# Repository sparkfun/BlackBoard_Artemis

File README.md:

SparkFun BlackBoard Artemis
============================

[  
*SparkFun BlackBoard (SPX-15332)*](https://www.sparkfun.com/products/15332)

Think of the BlackBoard Artemis as just another Arduino... That has BLE. And one meg of flash. And runs at less than 1mA. Oh, and it can run TensorFlow models. Ya, that too. The BlackBoard Artemis takes the incredibly powerful Artemis module from SparkFun and wraps it up in an easy to use and familiar Uno footprint. We've written an Arduino core from scratch to make programming the Artemis as familiar as `Serial.begin(9600)`. Time-to-first-blink is less than five minutes.

The BlackBoard Artemis has the improved power conditioning and USB to serial that we've refined over the years on our BlackBoard line of products. A modern USB-C connector makes programming easy. A Qwiic connector makes I<sup>2</sup>C easy. The BlackBoard Artemis is fully compatible with SparkFun's Arduino core and can be programmed easily under the Arduino IDE. We've exposed the JTAG connector for more advanced users who prefer to use the power and speed of professional tools. We've added a digital MEMS microphone for folks wanting to experiment with always-on voice commands with TensorFlow and machine learning. We've even added a convenient jumper to measure current consumption for low power testing.

With 1M flash and 384k RAM you'll have plenty of room for your sketches. The Artemis module runs at 48MHz with a 96MHz turbo mode available and with Bluetooth to boot!

The SparkFun BlackBoard Artemis is a great platform to 'kick the tires' of this amazing module. If you're interesting in testing out the full capabilities of the SparkFun Artemis module or if you're looking for more compact solution, be sure to checkout our ATP and Nano versions of the Artemis line.

**Note:** We are actively working on getting FCC and compliance certifications for the SparkFun Artemis Module. Once our certifications are complete we will be moving the BlackBoard to a RedBoard format with the FCC Certified version of the Artemis on board. *Please be aware* that this could happen as soon as a few weeks to a month so this BlackBoard version is for those of you who can't wait and want to start using the SparkFun Artemis as soon as possible!

Repository Contents
-------------------
* **/Hardware** - Eagle design files (.brd, .sch)

Documentation
-------------------
* **[Hookup Guide for the BlackBoard Artemis](https://learn.sparkfun.com/tutorials/hookup-guide-for-the-blackboard-artemis)**
* **[Designing with the SparkFun Artemis](https://learn.sparkfun.com/tutorials/designing-with-the-sparkfun-artemis)** - Layout and design considerations when using the Artemis module.
* **[Artemis Development with Arduino](https://learn.sparkfun.com/tutorials/artemis-development-with-arduino)** - Introduction to the Arduino core for the Artemis Module.
* **[Ambiq Apollo3 SDK SetUp](https://learn.sparkfun.com/tutorials/using-sparkfun-edge-board-with-ambiq-apollo3-sdk)** - Getting set up with the Apollo3 Software Development Kit.
* **[CH340E USB to serial IC Drivers](https://www.sparkfun.com/ch340)**
* **[SparkFun Fritzing repo](https://github.com/sparkfun/Fritzing_Parts)** - Fritzing diagrams for SparkFun products.
License Information
-------------------

This product is _**open source**_! 

Please review the LICENSE.md file for license information. 

If you have any questions or concerns on licensing, please contact techsupport@sparkfun.com.

Please use, reuse, and modify these files as you see fit. Please maintain attribution to SparkFun Electronics and release any derivative under the same license.

Distributed as-is; no warranty is given.

- Your friends at SparkFun.

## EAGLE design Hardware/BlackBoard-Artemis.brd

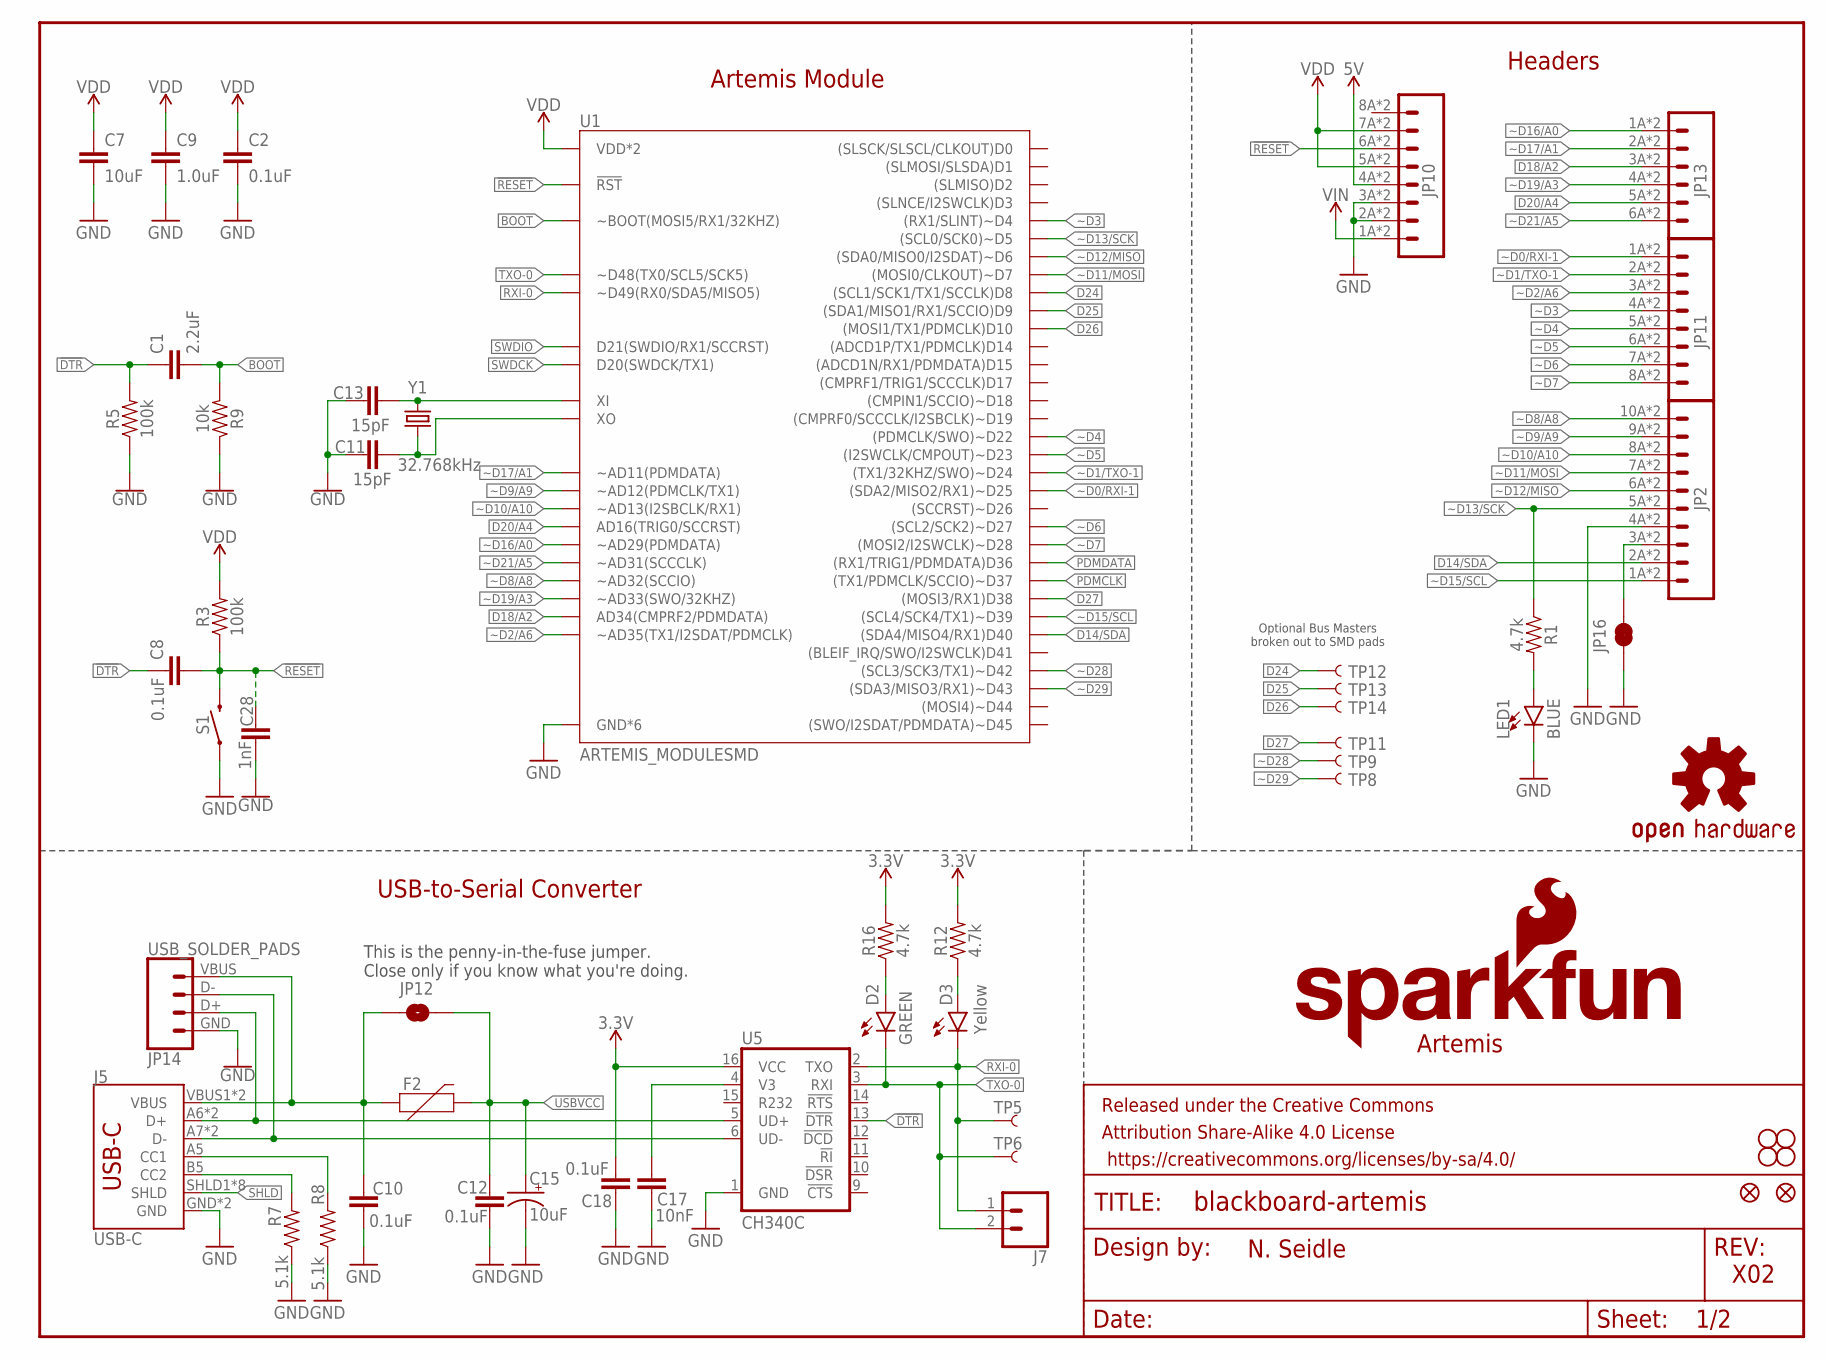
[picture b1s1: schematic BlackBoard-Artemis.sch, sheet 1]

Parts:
C1: 2.2uF; 0603
C2, C8, C10, C12, C18: 0.1uF; 0603
C7: 10uF; 0603
C9: 1.0uF; 0603
C11, C13: 15pF; 0603
C15: 10uF; EIA3216
C17: 10nF; 0603
C28: 1nF; 0603
D2: GREEN; LED-1206
D3: Yellow; LED-1206
F2: 6V/2A; 1210
FRAME1: FRAME-LETTER; CREATIVE_COMMONS
J5: USB-C; USB-C-16P
J7: CONN_021X02_NO_SILK; 1X02_NO_SILK
JP1: SFE_LOGO_NAME.1_INCH; SFE_LOGO_NAME_.1
JP2: M10SMD_COMBO; 1X10_SMD_COMBINED
JP3, JP4, JP5, JP6: STAND-OFF
JP7: SFE_LOGO_FLAME.1_INCH; SFE_LOGO_FLAME_.1
JP8, JP9: FIDUCIAL1X2; FIDUCIAL-1X2
JP10: M08SMD-COMBO; 1X08_SMD_COMBINED
JP11: JP11; 1X08_SMD_COMBINED
JP12: JUMPER-SMT_2_NO_SILK; SMT-JUMPER_2_NO_SILK
JP13: M06SMD-STRAIGHT-COMBO; 1X06_SMD_STRAIGHT_COMBO
JP14: USB_SOLDER_PADS; USB-SOLDER-PADS
JP16: JUMPER-SMT_2_NC_TRACE_SILK; SMT-JUMPER_2_NC_TRACE_SILK
LED1: BLUE; LED-1206
R1, R12, R16: 4.7k; 0603
R3, R5: 100k; 0603
R7, R8: 5.1k; 0603
R9: 10k; 0603
S1: MOMENTARY-SWITCH-SPST-SMD-5.2-TALL-REDUNDANT; TACTILE_SWITCH_SMD_5.2MM
TP5, TP6, TP8, TP9, TP11, TP12, TP13, TP14: TEST-POINT3X5; PAD.03X.05
U1: ARTEMIS_MODULESMD; ARTEMIS_FP
U5: CH340C; SO016
U$16: OSHW-LOGOS; OSHW-LOGO-S
Y1: 32.768kHz; CRYSTAL-SMD-3.2X1.5MM

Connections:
3.3V: C18.1, R12.2, R16.2, U5.16 (VCC); also elsewhere on the board
5V: JP10.4A (4), JP10.4B (4); also elsewhere on the board
!DTR: C1.1, C8.1, R5.2, U5.13 (!DTR)
!RESET: C8.2, C28.1, JP10.6A (6), JP10.6B (6), R3.1, S1.3 (2), S1.4 (2), U1.~RST (!RST); also elsewhere on the board
BOOT: C1.2, R9.2, U1.BOOT (~BOOT(MOSI5/RX1/32KHZ))
CC1: J5.A5 (CC1), R8.2
CC2: J5.B5 (CC2), R7.2
D14/SDA: JP2.2A (2), JP2.2B (2), U1.D40 ((SDA4/MISO4/RX1)D40); also elsewhere on the board
D18/A2: JP13.3A (3), JP13.3B (3), U1.AD34 (AD34(CMPRF2/PDMDATA))
D20/A4: JP13.5A (5), JP13.5B (5), U1.AD16 (AD16(TRIG0/SCCRST))
D24: TP12.P$1, U1.D8 ((SCL1/SCK1/TX1/SCCLK)D8)
D25: TP13.P$1, U1.D9 ((SDA1/MISO1/RX1/SCCIO)D9)
D26: TP14.P$1, U1.D10 ((MOSI1/TX1/PDMCLK)D10)
D27: TP11.P$1, U1.D38 ((MOSI3/RX1)D38)
D+: J5.A6 (D+), J5.B6 (D+), JP14.D+ (3), U5.5 (UD+)
D-: J5.A7 (D-), J5.B7 (D-), JP14.D- (2), U5.6 (UD-)
GND: C2.1, C7.2, C9.2, C10.2, C11.1, C12.2, C13.1, C15.-, C17.2, C18.2, C28.2, J5.GND, J5.GND2 (GND), JP2.4A (4), JP2.4B (4), JP10.2A (2), JP10.2B (2), JP10.3A (3), JP10.3B (3), JP14.GND (4), JP16.1, LED1.C, R5.1, R7.1, R8.1, R9.1, S1.1, S1.2 (1), U1.GND@1 (GND*6), U1.GND@22 (GND*6), U1.GND@38 (GND*6), U1.GND@39 (GND*6), U1.GND@47 (GND*6), U1.GND@59 (GND*6), U5.1 (GND); also elsewhere on the board
unnamed: LED1.A, R1.2
unnamed: D2.A, R16.1
unnamed: C17.1, U5.4 (V3)
unnamed: C11.2, U1.XO, Y1.P$2 (2)
unnamed: C13.2, U1.XI, Y1.P$1 (1)
unnamed: D3.A, R12.1
unnamed: JP2.3A (3), JP2.3B (3), JP16.2
PDMCLK: U1.~D37 ((TX1/PDMCLK/SCCIO)~D37); also elsewhere on the board
PDMDATA: U1.D36 ((RX1/TRIG1/PDMDATA)D36); also elsewhere on the board
RXI-0: D3.C, J7.1, TP5.P$1, U1.RXI-0 (~D49(RX0/SDA5/MISO5)), U5.2 (TXO)
SHLD: J5.SHLD1 (SHLD), J5.SHLD2 (SHLD), J5.SHLD3 (SHLD), J5.SHLD4 (SHLD), J5.SHLD5 (SHLD), J5.SHLD6 (SHLD), J5.SHLD7 (SHLD), J5.SHLD8 (SHLD)
SWDCK: U1.SWDCK (D20(SWDCK/TX1)); also elsewhere on the board
SWDIO: U1.SWDIO (D21(SWDIO/RX1/SCCRST)); also elsewhere on the board
TXO-0: D2.C, J7.2, TP6.P$1, U1.TXO-0 (~D48(TX0/SCL5/SCK5)), U5.3 (RXI)
USBVCC: C12.1, C15.+, F2.2, JP12.2; also elsewhere on the board
VDD: C2.2, C7.1, C9.1, JP10.5A (5), JP10.5B (5), JP10.7A (7), JP10.7B (7), R3.2, U1.VDD@36 (VDD*2), U1.VDD@37 (VDD*2); also elsewhere on the board
VIN: JP10.1A (1), JP10.1B (1); also elsewhere on the board
VUSB: C10.1, F2.1, J5.VBUS1 (VBUS), J5.VBUS2 (VBUS), JP12.1, JP14.VBUS (1)
~D0/RXI-1: JP11.1A (1), JP11.1B (1), U1.~D25 ((SDA2/MISO2/RX1)~D25)
~D1/TXO-1: JP11.2A (2), JP11.2B (2), U1.~D24 ((TX1/32KHZ/SWO)~D24)
~D2/A6: JP11.3A (3), JP11.3B (3), U1.~AD35 (~AD35(TX1/I2SDAT/PDMCLK))
~D3: JP11.4A (4), JP11.4B (4), U1.~D4 ((RX1/SLINT)~D4)
~D4: JP11.5A (5), JP11.5B (5), U1.~D22 ((PDMCLK/SWO)~D22)
~D5: JP11.6A (6), JP11.6B (6), U1.~D23 ((I2SWCLK/CMPOUT)~D23)
~D6: JP11.7A (7), JP11.7B (7), U1.~D27 ((SCL2/SCK2)~D27)
~D7: JP11.8A (8), JP11.8B (8), U1.~D28 ((MOSI2/I2SWCLK)~D28)
~D8/A8: JP2.10A (10), JP2.10B (10), U1.~AD32 (~AD32(SCCIO))
~D9/A9: JP2.9A (9), JP2.9B (9), U1.~AD12 (~AD12(PDMCLK/TX1))
~D10/A10: JP2.8A (8), JP2.8B (8), U1.~AD13 (~AD13(I2SBCLK/RX1))
~D11/MOSI: JP2.7A (7), JP2.7B (7), U1.D7 ((MOSI0/CLKOUT)~D7)
~D12/MISO: JP2.6A (6), JP2.6B (6), U1.~D6 ((SDA0/MISO0/I2SDAT)~D6)
~D13/SCK: JP2.5A (5), JP2.5B (5), R1.1, U1.~D5 ((SCL0/SCK0)~D5)
~D15/SCL: JP2.1A (1), JP2.1B (1), U1.~D39 ((SCL4/SCK4/TX1)~D39); also elsewhere on the board
~D16/A0: JP13.1A (1), JP13.1B (1), U1.~AD29 (~AD29(PDMDATA))
~D17/A1: JP13.2A (2), JP13.2B (2), U1.~AD11 (~AD11(PDMDATA))
~D19/A3: JP13.4A (4), JP13.4B (4), U1.~AD33/SWO (~AD33(SWO/32KHZ)); also elsewhere on the board
~D21/A5: JP13.6A (6), JP13.6B (6), U1.~AD31 (~AD31(SCCCLK))
~D28: TP9.P$1, U1.~D42 ((SCL3/SCK3/TX1)~D42)
~D29: TP8.P$1, U1.~D43 ((SDA3/MISO3/RX1)~D43)

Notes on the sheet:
Artemis
USB-to-Serial Converter
N. Seidle
X02
This is the penny-in-the-fuse jumper. Close only if you know what you're doing.
Optional Bus Masters broken out to SMD pads
Artemis Module
Headers

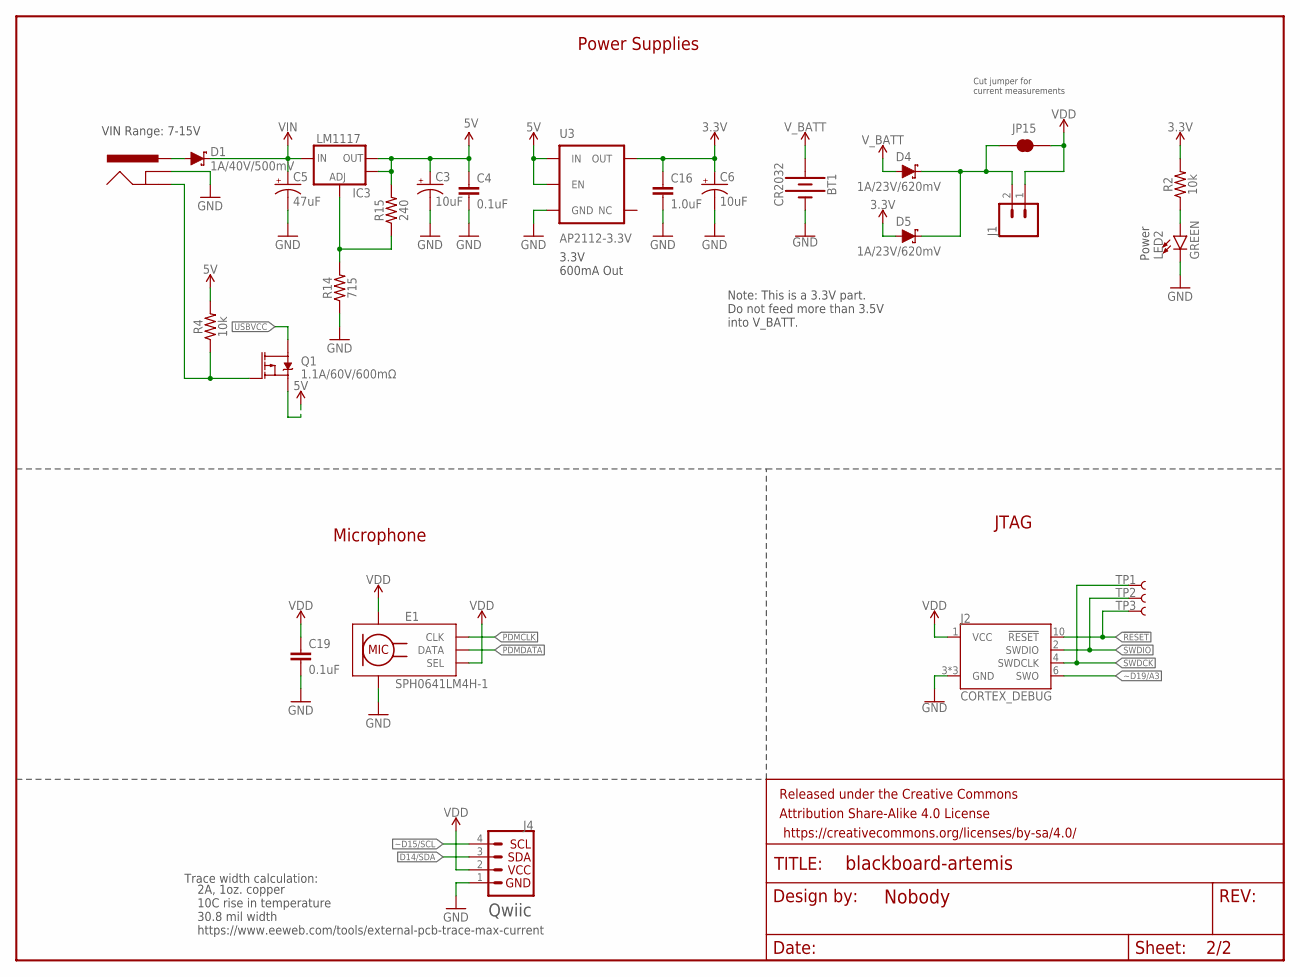
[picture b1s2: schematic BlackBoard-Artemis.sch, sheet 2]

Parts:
BT1: CR2032; BATTCON_20MM_4LEGS_OVERPASTE
C3, C6: 10uF; EIA3216
C4, C19: 0.1uF; 0603
C5: 47uF; PANASONIC_D
C16: 1.0uF; 0603
D1: 1A/40V/500mV; SMA-DIODE
D4, D5: 1A/23V/620mV; SOD-323
E1: SPH0641LM4H-1; SPH0641LM4H-1_MICROPHONE
FRAME2: FRAME-LETTERNO_PACKAGE; DUMMY
IC3: LM1117; SOT223-ALT1
J1: CONN_021X02_NO_SILK; 1X02_NO_SILK
J2: CORTEX_DEBUG; 2X5-PTH-1.27MM-NO_SILK
J3: POWER_JACKTOE; POWER_JACK_SMD_OVERPASTE_TOE
J4: QWIIC_CONNECTORJS-1MM; JST04_1MM_RA
JP15: JUMPER-SMT_2_NC_TRACE_SILK; SMT-JUMPER_2_NC_TRACE_SILK
LED2: GREEN; LED-1206
Q1: 1.1A/60V/600mΩ; SOT23-3
R2, R4: 10k; 0603
R14: 715; 0603
R15: 240; 0603
TP1, TP2, TP3: TEST-POINT3X5; PAD.03X.05
U3: AP2112-3.3V; SOT23-5

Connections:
3.3V: C6.+, C16.1, D5.A, R2.2, U3.5 (OUT); also elsewhere on the board
5V: C3.+, C4.1, IC3.2 (OUT), IC3.4 (OUT), Q1.2 (S), R4.2, R15.2, U3.1 (IN), U3.3 (EN); also elsewhere on the board
!RESET: J2.10 (!RESET), TP3.P$1; also elsewhere on the board
D14/SDA: J4.3; also elsewhere on the board
GND: BT1.2 (-), C3.-, C4.2, C5.-, C6.-, C16.2, C19.2, E1.3 (GND), E1.6 (GND), E1.7 (GND), E1.8 (GND), J2.3 (GND), J2.5 (GND), J2.9 (GND), J3.GND (GNDBREAK), J4.1, LED2.C, R14.1, U3.2 (GND); also elsewhere on the board
INSERT: J3.P$4 (GND), Q1.1 (G), R4.1
unnamed: LED2.A, R2.1
unnamed: D4.C, D5.C, J1.2, JP15.1
unnamed: IC3.1 (ADJ), R14.2, R15.1
PDMCLK: E1.4 (CLK); also elsewhere on the board
PDMDATA: E1.1 (DATA); also elsewhere on the board
PWRIN: D1.A, J3.VIN0 (PWR)
SWDCK: J2.4 (SWDCLK), TP1.P$1; also elsewhere on the board
SWDIO: J2.2 (SWDIO), TP2.P$1; also elsewhere on the board
USBVCC: Q1.3 (D); also elsewhere on the board
VDD: C19.1, E1.2 (SEL), E1.5 (VDD), J1.1, J2.1 (VCC), J4.2, JP15.2; also elsewhere on the board
VIN: C5.+, D1.C, IC3.3 (IN); also elsewhere on the board
V_BATT: BT1.1 (+), D4.A
~D15/SCL: J4.4; also elsewhere on the board
~D19/A3: J2.6 (SWO); also elsewhere on the board

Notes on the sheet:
VIN Range: 7-15V
3.3V 600mA Out
Cut jumper for current measurements
Power Supplies
Microphone
Note: This is a 3.3V part. Do not feed more than 3.5V into V_BATT.
Qwiic
Trace width calculation:
2A, 1oz. copper 10C rise in temperature 30.8 mil width https://www.eeweb.com/tools/external-pcb-trace-max-current
JTAG
Power

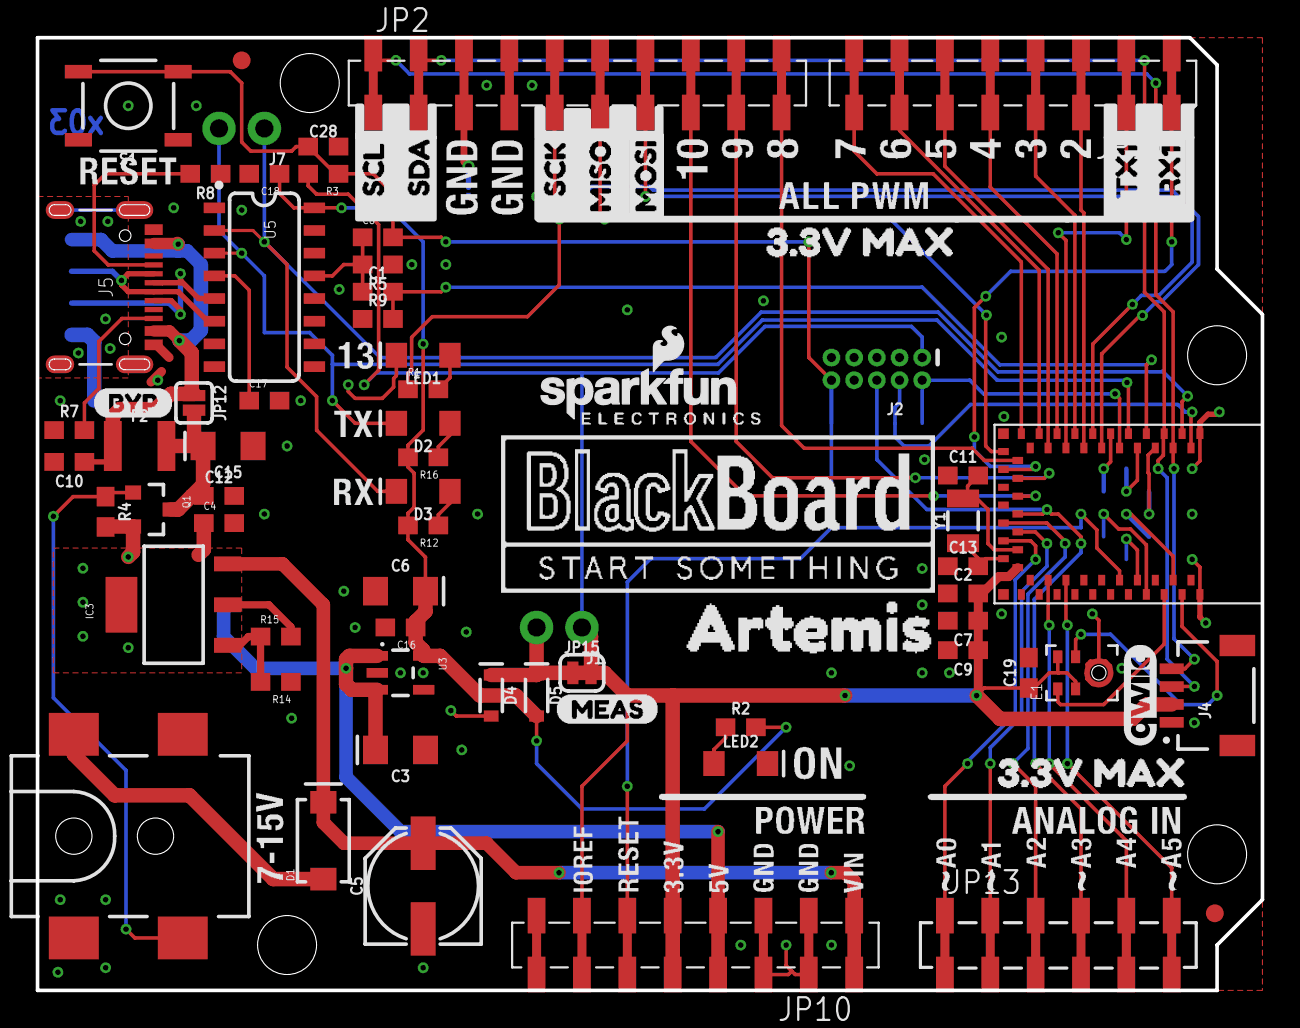
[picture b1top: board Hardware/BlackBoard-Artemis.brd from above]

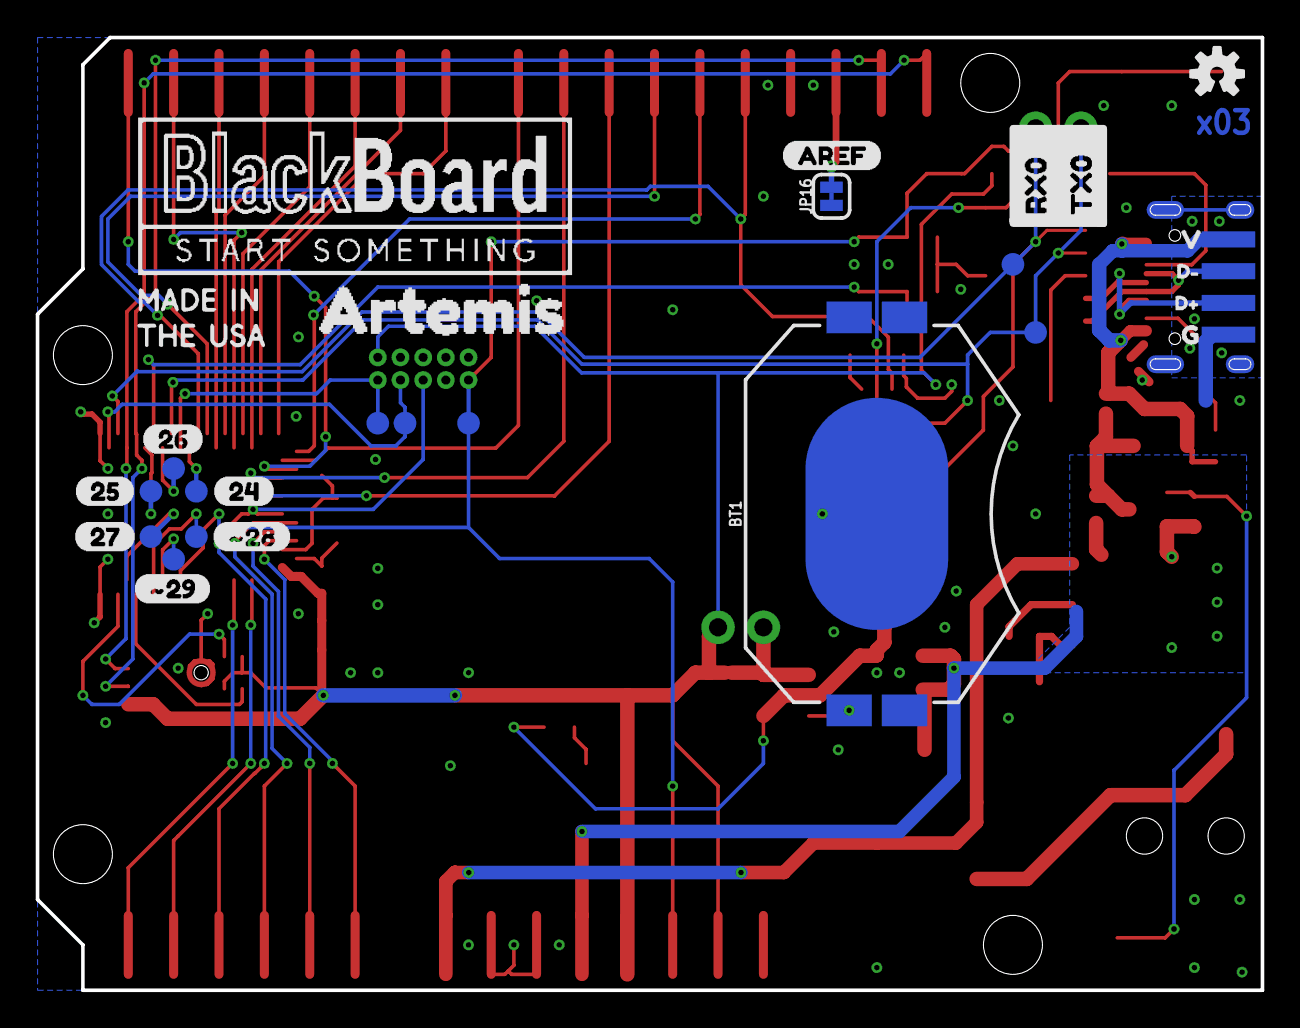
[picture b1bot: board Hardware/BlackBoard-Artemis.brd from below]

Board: 2 copper layers, 68.6 x 53.3 mm, 114 parts (32 on the bottom side), 62 nets.

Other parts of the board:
U$1, U$3: BLACKBOARDLOGO#PNG
U$2: D#3
U$4: MADEINUSA#PNG
U$9: QWIIC_COPYRIGHT_SMALL
U$10: D#4
U$11: G1
U$12: V0
U$13, U$67: 3#3V_MAX2
U$14, U$15: ARTEMIS0
U$17: #284
U$18: SCL1
U$19: #295
U$20: AREF2
U$21: 240
U$22: SDA0
U$23: 251
U$24: 262
U$25: 273
U$47: MISO8
U$48: MOSI7
U$49: RX01
U$50: SCK9
U$53: TX00
U$68: BYP0
U$70: MEAS3
U$71: RX11
U$72: TX10

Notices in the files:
parts and their libraries:
SparkFun-Aesthetics: Licensing: CC v3.0 Share-Alike You are welcome to use this library for commercial purposes.
SparkFun-Aesthetics: Released under the Creative Commons Attribution Share-Alike 4.0 License
SparkFun-Aesthetics: https://creativecommons.org/licenses/by-sa/4.0
